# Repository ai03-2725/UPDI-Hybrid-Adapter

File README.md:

# UPDI-Hybrid-Adapter

A CH340E-based USB-to-UPDI/serial hybrid adapter  
Designed for convenient programming and debugging of newer AVR devices.

**Warning:** Currently untested.
It is based on tested circuitry so it *should* work, but proceed at your own risk until I produce one myself and confirm its functionality.

## Features

- Practicality 
  - Small 19 x 47mm form factor, connects via USB-C
  - Most components inset 1mm from the board edge to prevent accidental damage during use
  - Components only on topside for affordable PCBA and easy reflow assembly
  - Can be ordered fully assembled using JLCPCB's economic PCBA service
- Safety
  - ESD protection on USB port
  - Fused at both USB connector and output for double overcurrent protection
- Functionality
  - Selectable output voltage (5V and 3.3V)
  - Selectable UPDI programming mode or serial communications mode (TX/RX)
  - Status LEDs for data output, board power, and output/target power
  - 2x3 pin header compatible with the Tag-Connect TC2030-IDC-NL
  - 1x3 pin header for UPDI-only use

## Pinout

Please double-check the pinout and connector orientation with the silkscreen markings on the PCB.

6-pin
```
  Pin 1
|-------|-------|
| UPDI  | VCC   |
|-------|-------|
|       | TX    |
|-------|-------|
| RX    | GND   |
|-------|-------|
          Pin 6
```

3-pin
```
  Pin 1
|-------|
| UPDI  |
|-------|
| GND   |
|-------|
| VCC   |
|-------|
  Pin 3
```

## Credits

Effectively all circuitry credits go to [wagiminator's SerialUPDI Programmer](https://github.com/wagiminator/AVR-Programmer/tree/master/SerialUPDI_Programmer); the only things I did were switching out the USB connector and adding the switch to toggle the CH340's output between UPDI wiring and direct TX/RX connection.  

This project is released under the same [license](https://github.com/ai03-2725/UPDI-Hybrid-Adapter/blob/main/LICENSE) as the above.

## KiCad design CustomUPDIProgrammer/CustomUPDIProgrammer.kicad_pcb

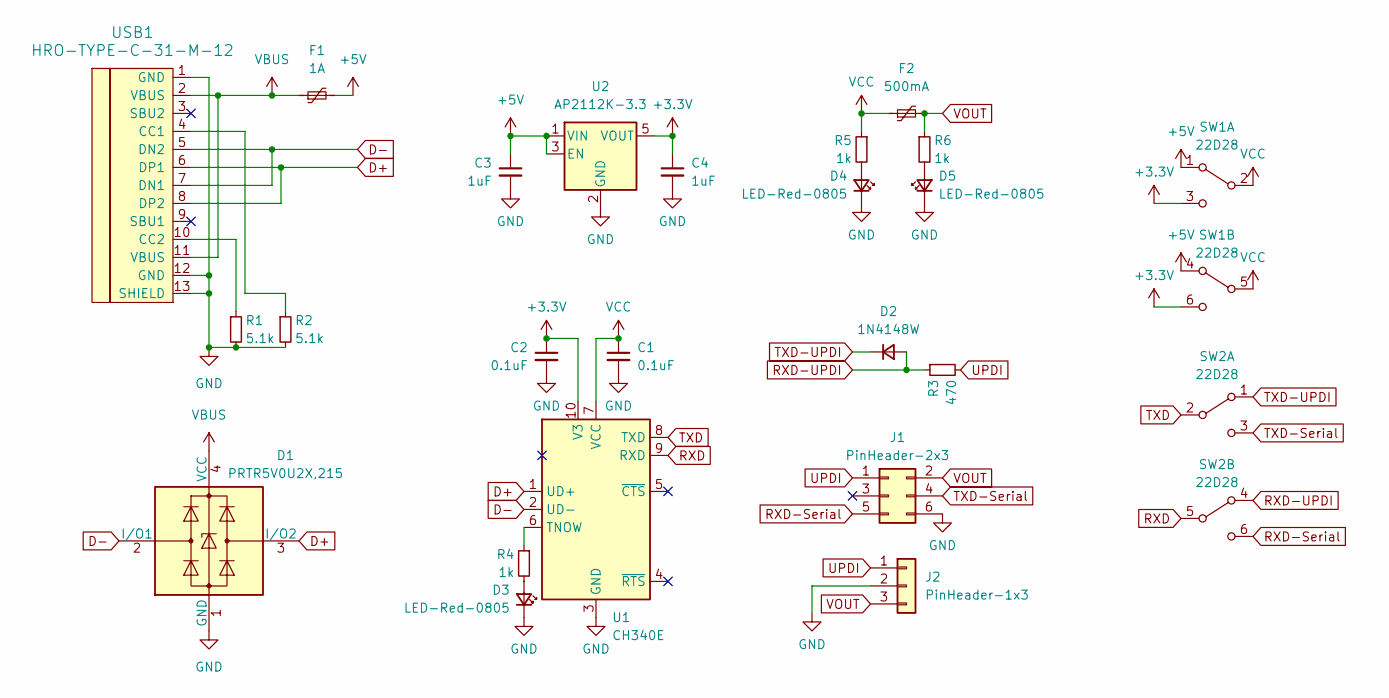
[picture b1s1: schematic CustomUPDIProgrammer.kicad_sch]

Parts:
C1, C2: 0.1uF; C_0603_1608Metric
C3, C4: 1uF; C_0603_1608Metric
D1: PRTR5V0U2X,215; SOT143B
D2: 1N4148W; D_SOD-123
D3, D4, D5: LED-Red-0805; LED_0603_1608Metric
F1: 1A; Fuse_1206_3216Metric
F2: 500mA; Fuse_1206_3216Metric
J1: PinHeader-2x3; PinHeader_2x03_DC3
J2: PinHeader-1x3; PinHeader_1x03_P2.54mm_Vertical
R1, R2: 5.1k; R_0603_1608Metric
R3: 470; R_0603_1608Metric
R4, R5, R6: 1k; R_0603_1608Metric
SW1, SW2: 22D28; MS-22D28-G020
U1: CH340E; MSOP-10_3x3mm_P0.5mm
U2: AP2112K-3.3; SOT-23-5
USB1: HRO-TYPE-C-31-M-12; HRO-TYPE-C-31-M-12-Assembly

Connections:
+3.3V: C2.1, C4.1, SW1.3 (C), SW1.6 (C), U1.10 (V3), U2.5 (VOUT)
+5V: C3.1, F1.2, SW1.1 (A), SW1.4 (A), U2.1 (VIN), U2.3 (EN)
D+: D1.3 (I/O2), U1.1 (UD+), USB1.6 (DP1), USB1.8 (DP2)
D-: D1.2 (I/O1), U1.2 (UD-), USB1.5 (DN2), USB1.7 (DN1)
GND: C1.2, C2.2, C3.2, C4.2, D1.1 (GND), D3.1 (K), D4.1 (K), D5.1 (K), J1.6, J2.2, R1.2, R2.2, U1.3 (GND), U2.2 (GND), USB1.1 (GND), USB1.12 (GND), USB1.13 (SHIELD)
unnamed: D3.2 (A), R4.2
unnamed: D4.2 (A), R5.2
unnamed: D5.2 (A), R6.2
unnamed: R4.1, U1.6 (TNOW)
unnamed: R2.1, USB1.4 (CC1)
unnamed: R1.1, USB1.10 (CC2)
RXD: SW2.5 (B), U1.9 (RXD)
RXD-Serial: J1.5, SW2.6 (C)
RXD-UPDI: D2.2 (A), R3.1, SW2.4 (A)
TXD: SW2.2 (B), U1.8 (TXD)
TXD-Serial: J1.4, SW2.3 (C)
TXD-UPDI: D2.1 (K), SW2.1 (A)
UPDI: J1.1, J2.1, R3.2
VBUS: D1.4 (VCC), F1.1, USB1.2 (VBUS), USB1.11 (VBUS)
VCC: C1.1, F2.1, R5.1, SW1.2 (B), SW1.5 (B), U1.7 (VCC)
VOUT: F2.2, J1.2, J2.3, R6.1

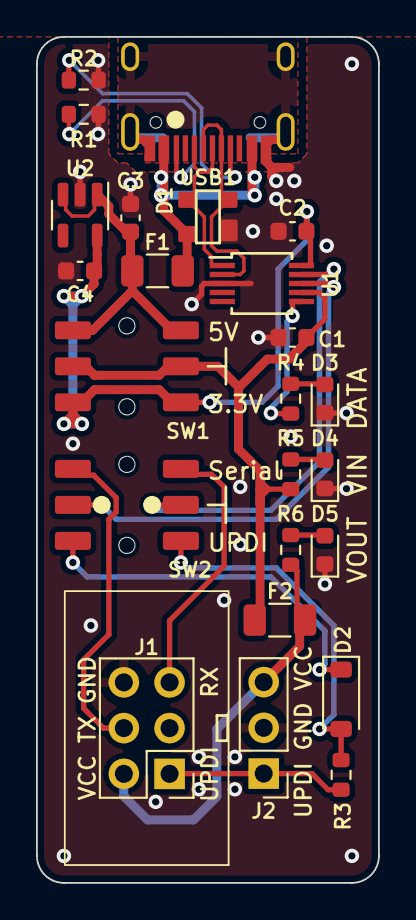
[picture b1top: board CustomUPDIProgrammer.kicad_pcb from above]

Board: 2 copper layers, 19.0 x 47.0 mm, 24 parts (0 on the bottom side), 21 nets.

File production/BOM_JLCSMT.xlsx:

Comment | Designator | Footprint | JLCPCB Part #（optional）
0.1uF | C1, C2 | Capacitor_SMD:C_0603_1608Metric | C14663
1uF | C3, C4 | Capacitor_SMD:C_0603_1608Metric | C15849
PRTR5V0U2X,215 | D1 | locallib:SOT143B | C12333
1N4148W | D2 | Diode_SMD:D_SOD-123 | C81598
LED-Red-0805 | D3, D4, D5 | LED_SMD:LED_0603_1608Metric | C2286
1A | F1 | Fuse:Fuse_1206_3216Metric | C910830
500mA | F2 | Fuse:Fuse_1206_3216Metric | C883126
PinHeader-2x3 | J1 | locallib:PinHeader_2x03_DC3 | C65114
PinHeader-1x3 | J2 | Connector_PinHeader_2.54mm:PinHeader_1x03_P2.54mm_Vertical | C49257
5.1k | R1, R2 | Resistor_SMD:R_0603_1608Metric | C23186
470 | R3 | Resistor_SMD:R_0603_1608Metric | C23182
1k | R4, R5, R6 | Resistor_SMD:R_0603_1608Metric | C21190
22D28 | SW1, SW2 | locallib:MS-22D28-G020 | C963205
CH340E | U1 | Package_SO:MSOP-10_3x3mm_P0.5mm | C99652
AP2112K-3.3 | U2 | Package_TO_SOT_SMD:SOT-23-5 | C51118
HRO-TYPE-C-31-M-12 | USB1 | Type-C:HRO-TYPE-C-31-M-12-Assembly | C165948

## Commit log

2023-12-30 Setup repo
2023-12-30 Add project files
2023-12-30 Add readme
2023-12-30 Add images to readme
2023-12-30 Rename source folder
2023-12-30 Export gerber and BOM
2023-12-30 Add prod files
